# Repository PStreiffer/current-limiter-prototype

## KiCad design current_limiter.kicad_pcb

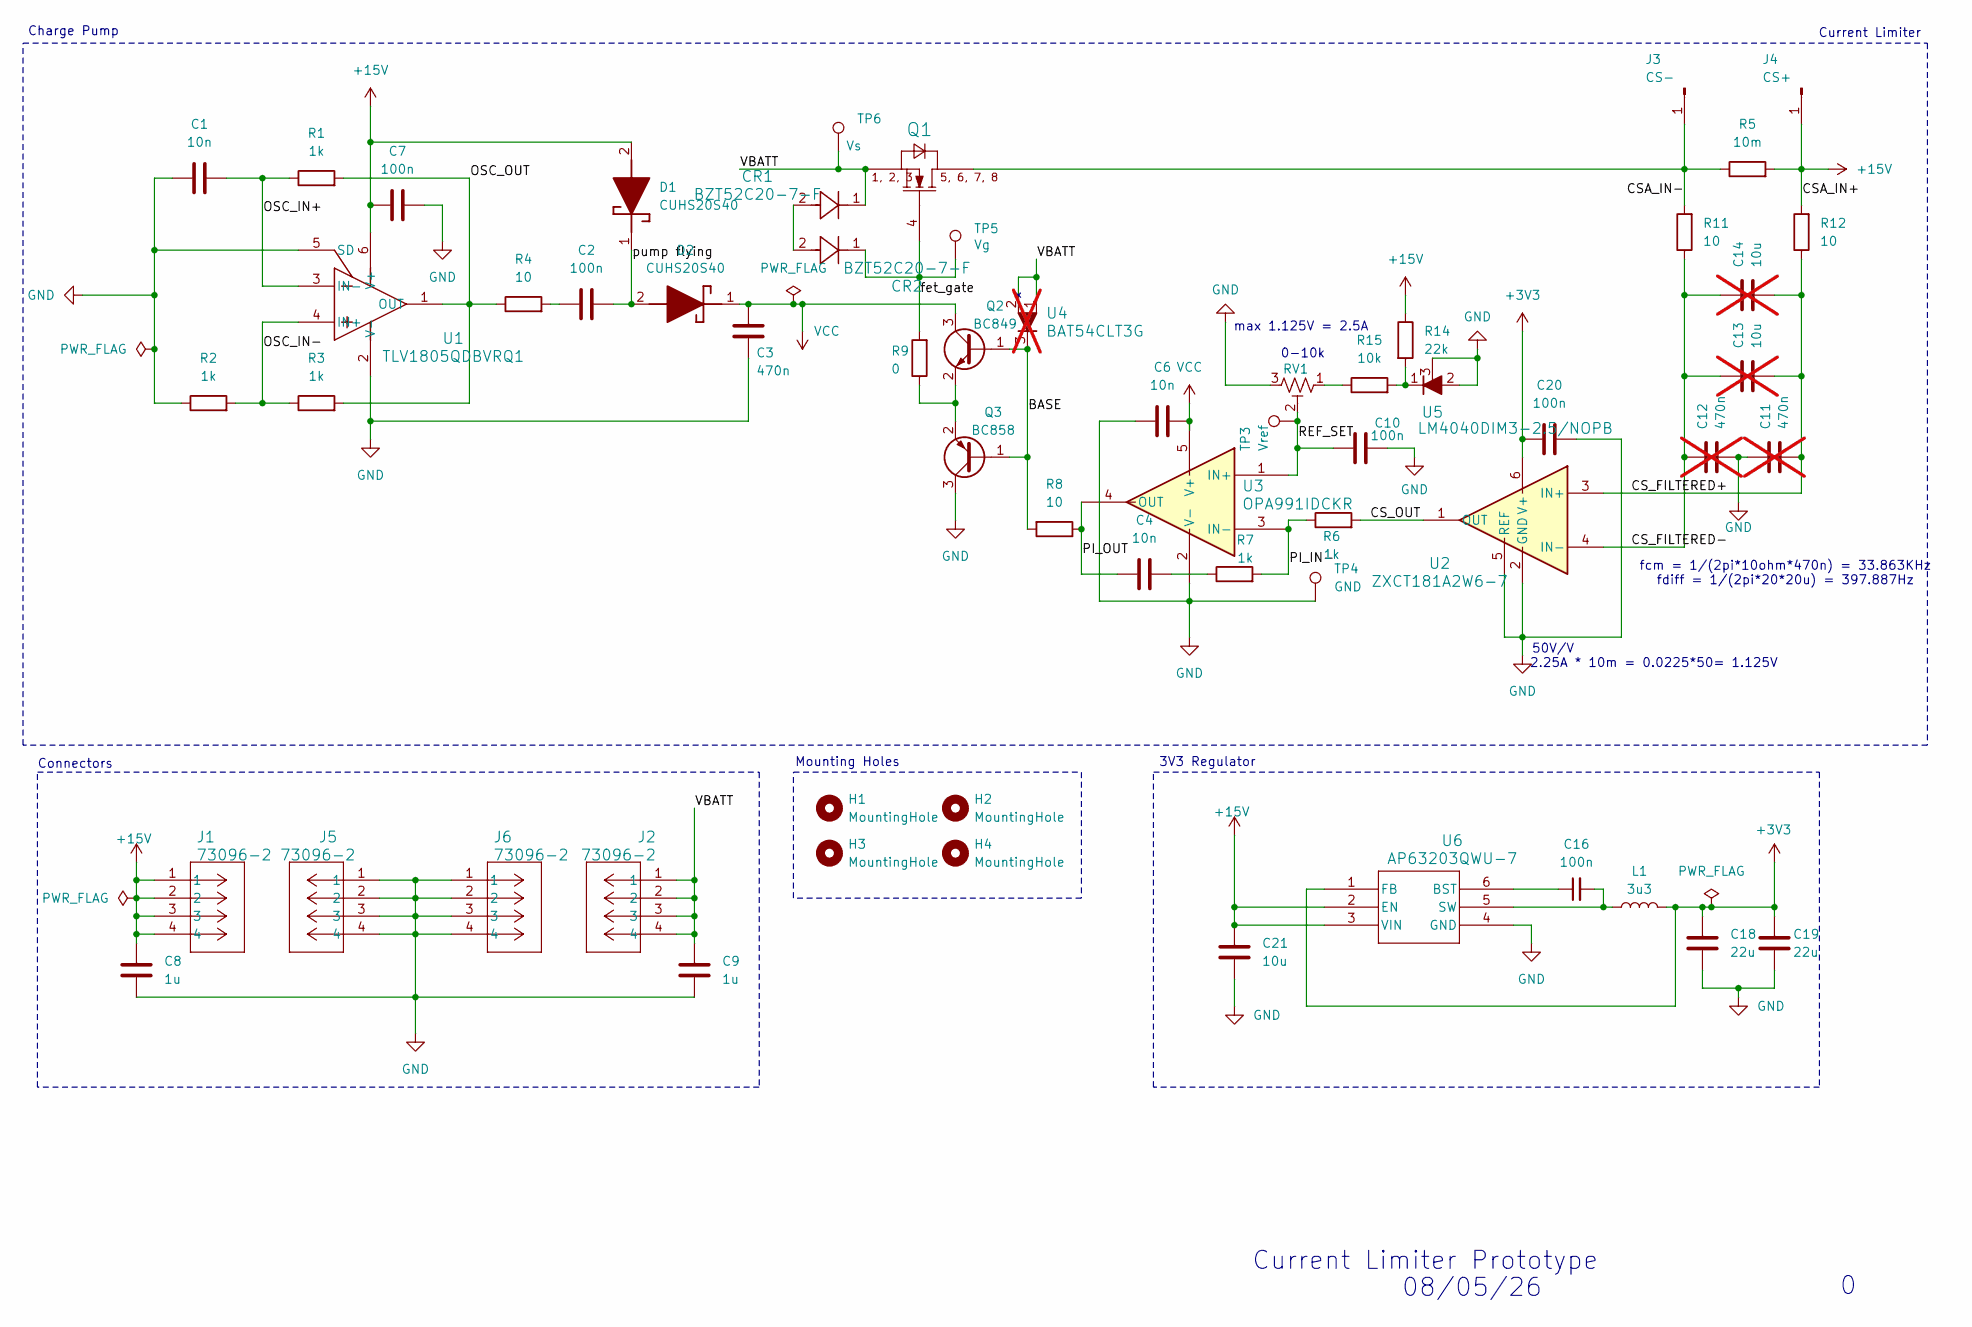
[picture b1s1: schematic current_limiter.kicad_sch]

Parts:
C1, C4, C6: 10n; C_0805_2012Metric
C2, C7, C10, C16, C20: 100n; C_0805_2012Metric
C3: 470n; C_0805_2012Metric
C8, C9: 1u; C_0805_2012Metric
C11, C12: 470n; C_0805_2012Metric; not fitted
C13, C14: 10u; C_0805_2012Metric; not fitted
C18, C19: 22u; C_0805_2012Metric
C21: 10u; C_0805_2012Metric
CR1, CR2: BZT52C20-7-F; SOD123_DIO
D1, D2: CUHS20S40; Manufacturer_Part_Number CUHS20S40
H1, H2, H3, H4: MountingHole; MountingHole_4.3mm_M4
J1, J2, J5, J6: 73096-2; CONN_73096-2_POM
J3: CS-; PinHeader_1x01_P1.27mm_Vertical
J4: CS+; PinHeader_1x01_P1.27mm_Vertical
L1: 3u3; IND_BOURNS_SDR0302
Q1: ISC025N08NM5LF2; INF-PG-TDSON-8-SSO8
Q2: BC849; SOT-23
Q3: BC858; SOT-23
R1, R2, R3, R6, R7: 1k; R_0805_2012Metric
R4, R8, R11, R12: 10; R_0805_2012Metric
R5: 10m; R_0805_2012Metric
R9: 0; R_0805_2012Metric
R14: 22k; R_0805_2012Metric
R15: 10k; R_0805_2012Metric
RV1: R_Potentiometer_Trim_US; Potentiometer_Runtron_RM-063_Horizontal
TP3: Vref; TestPoint_Pad_D2.0mm
TP4: GND; TestPoint_Pad_D2.0mm
TP5: Vg; TestPoint_Pad_D2.0mm
TP6: Vs; TestPoint_Pad_D2.0mm
U1: TLV1805QDBVRQ1; DBV0006A_L
U2: ZXCT181A2W6-7; DBV0006A_L
U3: OPA991IDCKR; SC_91IDCKR_TEX
U4: BAT54CLT3G; SOT-23-3_1P4X3P040_ONS; not fitted
U5: LM4040DIM3-2.5/NOPB; DBZ3
U6: AP63203QWU-7; TSOT26_DIO

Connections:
+3V3: C18.1, C19.1, C20.1, L1.2, U2.6 (V+), U6.1 (FB)
+15V: C7.1, C8.1, C21.1, D1.2 (A), J1.1, J1.2, J1.3, J1.4, J4.1 (Pin_1_1), R5.2, R12.2, R14.1, U1.6 (V+), U6.2 (EN), U6.3 (VIN)
/BASE: Q2.1 (B), Q3.1 (B), R8.2, U4.3
/CSA_IN-: J3.1 (Pin_1_1), Q1.5 (DRAIN), Q1.6 (DRAIN), Q1.7 (DRAIN), Q1.8 (DRAIN), R5.1, R11.2
/CS_FILTERED+: C11.1, C13.1, C14.1, R12.1, U2.3 (IN+)
/CS_FILTERED-: C12.2, C13.2, C14.2, R11.1, U2.4 (IN-)
/CS_OUT: R6.2, U2.1 (OUT)
/OSC_IN+: C1.2, R1.1, U1.3 (IN-)
/OSC_IN-: R2.2, R3.1, U1.4 (IN+)
/OSC_OUT: R1.2, R3.2, R4.1, U1.1 (OUT)
/PI_IN-: R6.1, R7.2, U3.3 (IN-)
/PI_OUT: C4.1, R8.1, U3.4 (OUT)
/REF_SET: C10.2, RV1.2, TP3.1 (1_1), U3.1 (IN+)
/VBATT: C9.1, CR1.1, J2.1, J2.2, J2.3, J2.4, Q1.1 (SOURCE), Q1.2 (SOURCE), Q1.3 (SOURCE), TP6.1 (1_1), U4.1, U4.2
/fet_gate: CR2.1, Q1.4 (GATE), R9.2, TP5.1 (1_1)
/pump flying: C2.2, D1.1 (K), D2.2 (A)
GND: C1.1, C3.1, C6.1, C7.2, C8.2, C9.2, C10.1, C11.2, C12.1, C18.2, C19.2, C20.2, C21.2, J5.1, J5.2, J5.3, J5.4, J6.1, J6.2, J6.3, J6.4, Q3.3 (C), R2.1, RV1.3, TP4.1 (1_1), U1.2 (V-), U1.5 (SD), U2.2 (GND), U2.5 (REF), U3.2 (V-), U5.2, U5.3, U6.4 (GND)
unnamed: C2.1, R4.2
unnamed: C4.2, R7.1
unnamed: CR1.2, CR2.2
unnamed: Q2.2 (E), Q3.2 (E), R9.1
unnamed: R14.2, R15.2, U5.1
unnamed: R15.1, RV1.1
unnamed: C16.1, U6.6 (BST)
unnamed: C16.2, L1.1, U6.5 (SW)
VCC: C3.2, C6.2, D2.1 (K), Q2.3 (C), U3.5 (V+)

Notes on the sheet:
fcm = 1/(2pi*10ohm*470n) = 33.863KHz fdiff = 1/(2pi*20*20u) = 397.887Hz
Charge Pump
Connectors
0-10k
08/05/26
max 1.125V = 2.5A
50V/V
3V3 Regulator
Current Limiter
Mounting Holes
2.25A * 10m = 0.0225*50= 1.125V
Current Limiter Prototype

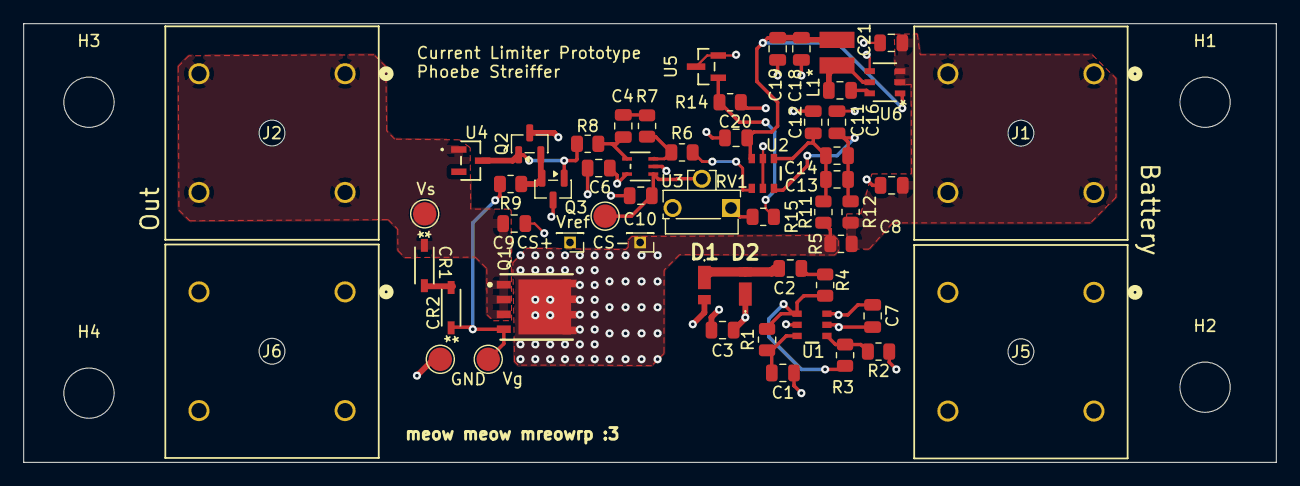
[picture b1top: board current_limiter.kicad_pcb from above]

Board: 4 copper layers, 107.2 x 37.5 mm, 60 parts (0 on the bottom side), 26 nets.

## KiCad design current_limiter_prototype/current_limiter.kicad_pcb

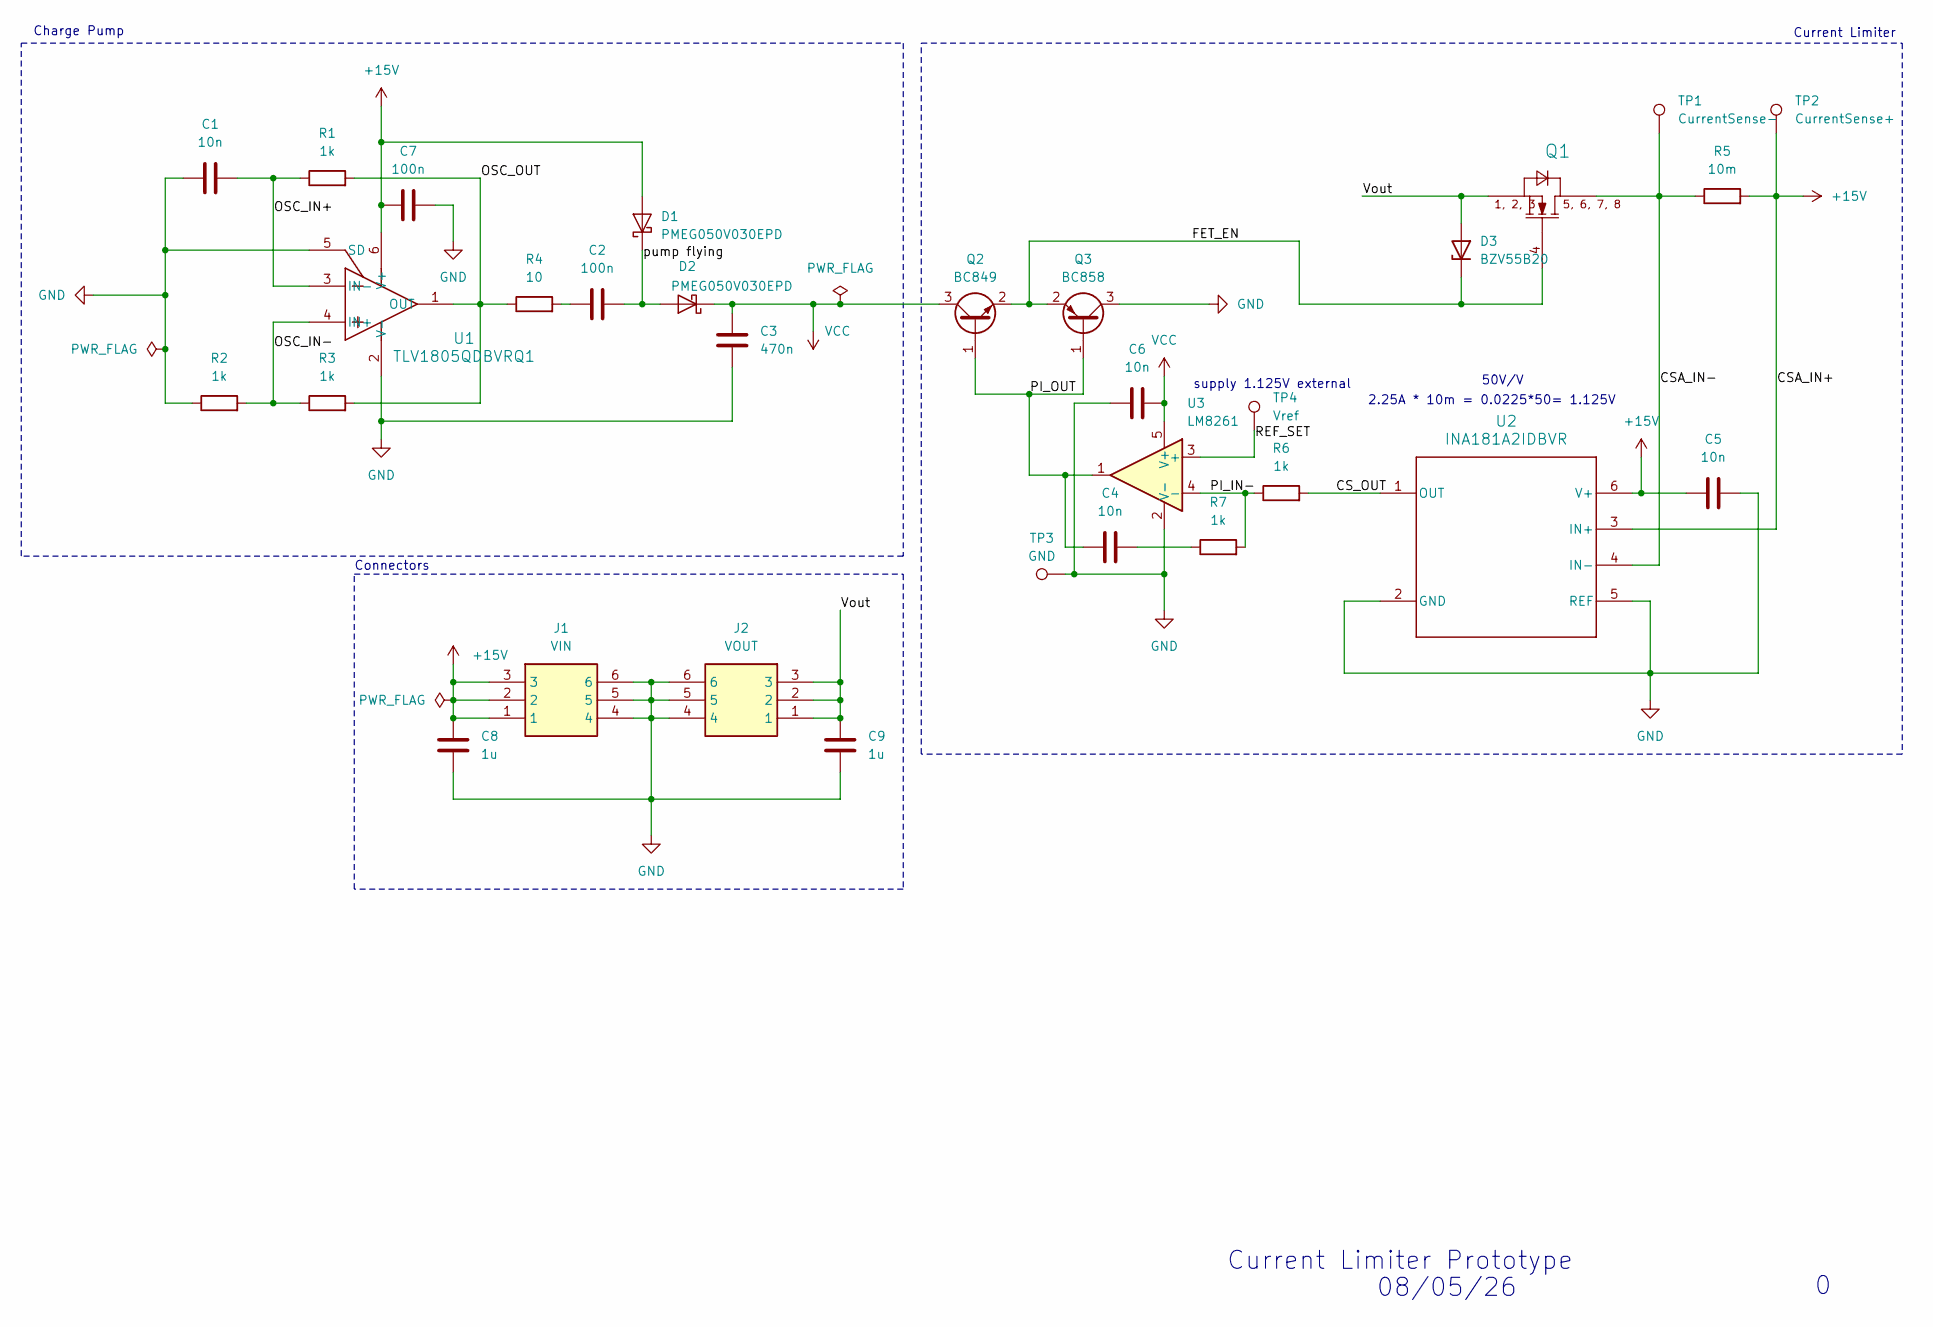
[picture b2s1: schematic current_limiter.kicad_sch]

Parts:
C1, C4, C5, C6: 10n; C_0504_1310Metric
C2, C7: 100n; C_0504_1310Metric
C3: 470n; C_0504_1310Metric
C8, C9: 1u; C_0504_1310Metric
D1, D2: PMEG050V030EPD; Nexperia_CFP15_SOT-1289
D3: BZV55B20; D_MiniMELF
J1: VIN; 4304506YY_6; Manufacturer_Part_Number 430450627
J2: VOUT; 4304506YY_6; Manufacturer_Part_Number 430450627
Q1: BSC040N10NS5; INF-PG-TDSON-8-SSO8
Q2: BC849; SOT-23
Q3: BC858; SOT-23
R1, R2, R3, R6, R7: 1k; R_0402_1005Metric
R4: 10; R_0402_1005Metric
R5: 10m; R_0402_1005Metric
TP1: CurrentSense-; TestPoint_THTPad_D4.0mm_Drill2.0mm
TP2: CurrentSense+; TestPoint_THTPad_D4.0mm_Drill2.0mm
TP3: GND; TestPoint_THTPad_D4.0mm_Drill2.0mm
TP4: Vref; TestPoint_THTPad_D4.0mm_Drill2.0mm
U1: TLV1805QDBVRQ1; DBV0006A_L
U2: INA181A2IDBVR; DBV0006A_L
U3: LM8261; SOT-23-5

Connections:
+15V: C5.1, C7.1, C8.1, D1.1 (A), D1.2 (A), J1.1, J1.2, J1.3, R5.2, TP2.1 (1_1), U1.6 (V+), U2.3 (IN+), U2.6 (V+)
/CSA_IN-: Q1.5 (DRAIN), Q1.6 (DRAIN), Q1.7 (DRAIN), Q1.8 (DRAIN), R5.1, TP1.1 (1_1), U2.4 (IN-)
/CS_OUT: R6.2, U2.1 (OUT)
/FET_EN: D3.1 (K), Q1.4 (GATE), Q2.2 (E), Q3.2 (E)
/OSC_IN+: C1.2, R1.1, U1.3 (IN-)
/OSC_IN-: R2.2, R3.1, U1.4 (IN+)
/OSC_OUT: R1.2, R3.2, R4.1, U1.1 (OUT)
/PI_IN-: R6.1, R7.2, U3.4 (-)
/PI_OUT: C4.1, Q2.1 (B), Q3.1 (B), U3.1
/REF_SET: TP4.1 (1_1), U3.3 (+)
/Vout: C9.1, D3.2 (A), J2.1, J2.2, J2.3, Q1.1 (SOURCE), Q1.2 (SOURCE), Q1.3 (SOURCE)
/pump flying: C2.2, D1.3 (K), D2.1 (A), D2.2 (A)
GND: C1.1, C3.1, C5.2, C6.1, C7.2, C8.2, C9.2, J1.4, J1.5, J1.6, J2.4, J2.5, J2.6, Q3.3 (C), R2.1, TP3.1 (1_1), U1.2 (V-), U1.5 (SD), U2.2 (GND), U2.5 (REF), U3.2 (V-)
unnamed: C2.1, R4.2
unnamed: C4.2, R7.1
VCC: C3.2, C6.2, D2.3 (K), Q2.3 (C), U3.5 (V+)

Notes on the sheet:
Charge Pump
Connectors
08/05/26
50V/V
supply 1.125V external
Current Limiter
2.25A * 10m = 0.0225*50= 1.125V
Current Limiter Prototype

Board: 2 copper layers, 31 parts (0 on the bottom side), 16 nets, no tracks yet.
